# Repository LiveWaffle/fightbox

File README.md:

# FightBox

## Description
The FightBox is a flexible custom built FightBox for fighting games.

## Why I Made it
#### I've Always struggled with wrist pain growing up due to breaking both of them. When i started playing tekken 7 i realized that playing with a traditional FightStick/Controller would cause tons of pain in my wrists. I wanted to design something that was smaller but still use-able and wouldn't hurt my hands after long hours of use.
---

## Pictures

| FightBox Fully Built | PCB |
|--------------------|--------------|
|  |  |

| Schematic | Case  |
|-----------------|----------------|
|  |  |

---
## Bill of Materials (BOM)

| Part                         | Qty | Footprint                 |
|------------------------------|-----|---------------------------|
| 1N4148WT Diode               | 12  | D_DO-35_SOD27_P7.62mm     |
| Cherry MX Switch             | 12  | SW_Cherry_MX_1.00u_PCB    |
| XIAO Seeed ESP32             | 1   | MCU_Seeed_ESP32C3         |
| TicKnot Arcade Button Caps   | 12  | MX Keycap Compatible      |

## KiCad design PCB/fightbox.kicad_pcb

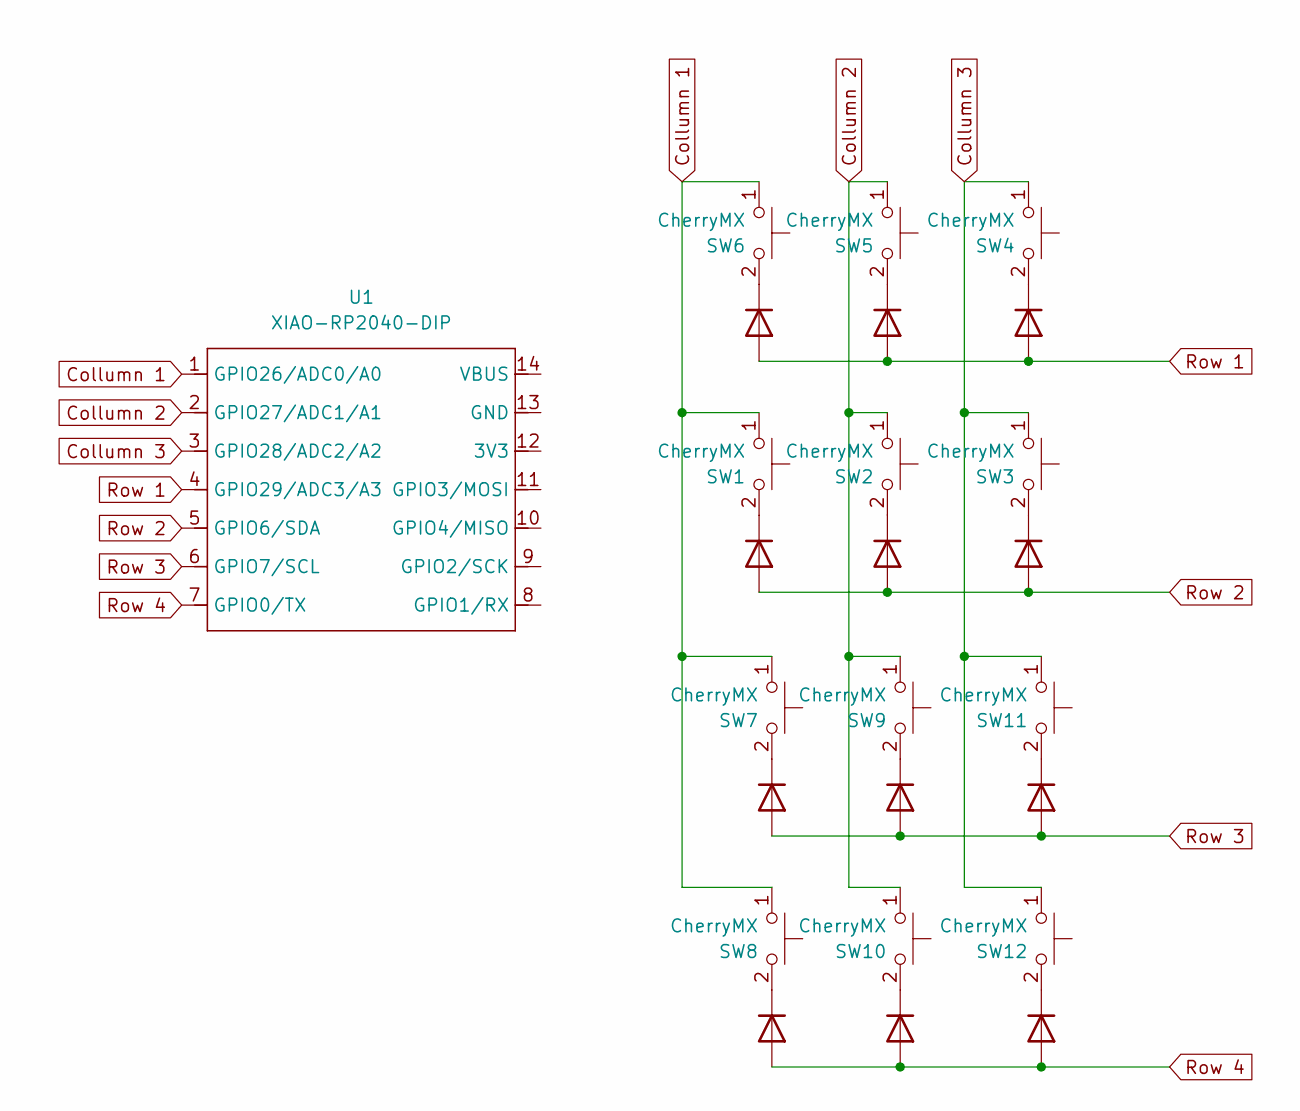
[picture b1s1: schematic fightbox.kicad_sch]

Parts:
D1, D2, D3, D4, D5, D6, D7, D8, D9, D10, D11, D12: 1N4148WT; D_DO-35_SOD27_P7.62mm_Horizontal
SW1, SW2, SW3, SW4, SW5, SW6, SW7, SW8, SW9, SW10, SW11, SW12: CherryMX; SW_Cherry_MX_1.00u_PCB
U1: XIAO-RP2040-DIP; MCU_Seeed_ESP32C3

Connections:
Collumn 1: SW1.1, SW6.1, SW7.1, SW8.1, U1.1 (GPIO26/ADC0/A0)
Collumn 2: SW2.1, SW5.1, SW9.1, SW10.1, U1.2 (GPIO27/ADC1/A1)
Collumn 3: SW3.1, SW4.1, SW11.1, SW12.1, U1.3 (GPIO28/ADC2/A2)
unnamed: D1.1 (K), SW6.2
unnamed: D2.1 (K), SW5.2
unnamed: D3.1 (K), SW4.2
unnamed: D4.1 (K), SW1.2
unnamed: D5.1 (K), SW2.2
unnamed: D6.1 (K), SW3.2
unnamed: D7.1 (K), SW7.2
unnamed: D8.1 (K), SW8.2
unnamed: D9.1 (K), SW9.2
unnamed: D10.1 (K), SW10.2
unnamed: D11.1 (K), SW11.2
unnamed: D12.1 (K), SW12.2
Row 1: D1.2 (A), D2.2 (A), D3.2 (A), U1.4 (GPIO29/ADC3/A3)
Row 2: D4.2 (A), D5.2 (A), D6.2 (A), U1.5 (GPIO6/SDA)
Row 3: D7.2 (A), D9.2 (A), D11.2 (A), U1.6 (GPIO7/SCL)
Row 4: D8.2 (A), D10.2 (A), D12.2 (A), U1.7 (GPIO0/TX)

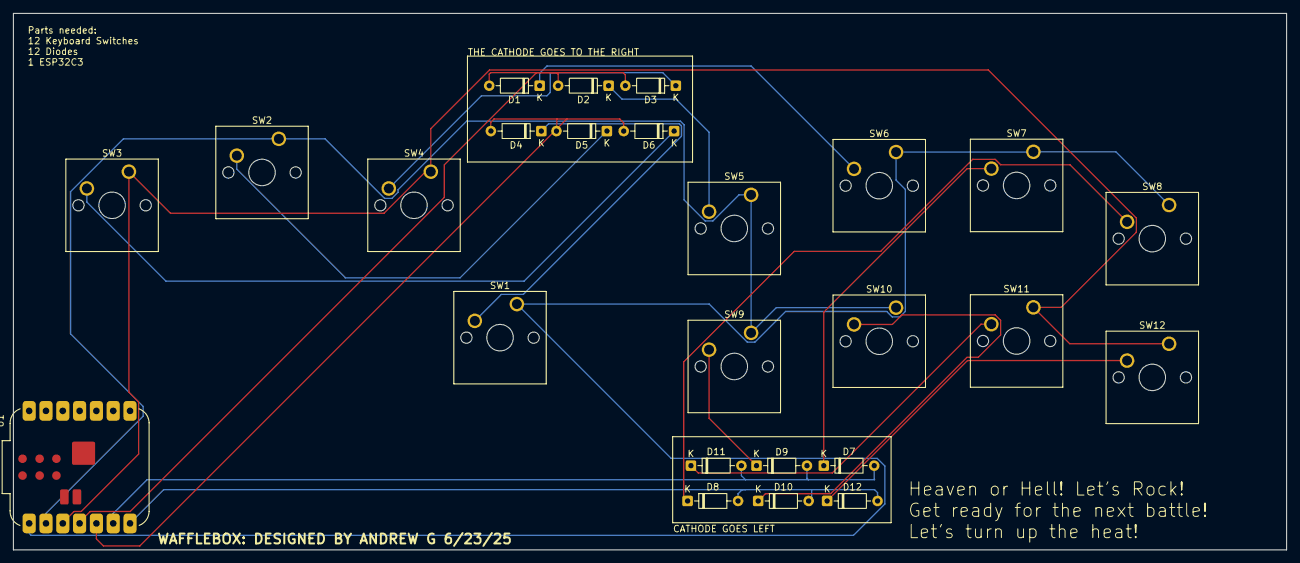
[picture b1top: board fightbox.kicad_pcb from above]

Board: 2 copper layers, 192.3 x 81.0 mm, 25 parts (0 on the bottom side), 19 nets.

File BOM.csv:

"Id";"Designator";"Footprint";"Quantity";"Designation";"Supplier and ref";
1;"D8,D4,D6,D9,D1,D2,D10,D5,D7,D11,D3,D12";"D_DO-35_SOD27_P7.62mm_Horizontal";12;"1N4148WT";;;
2;"SW12,SW2,SW4,SW5,SW3,SW1,SW9,SW6,SW7,SW11,SW8,SW10";"SW_Cherry_MX_1.00u_PCB";12;"CherryMX";;;
3;"U1";"MCU_Seeed_ESP32C3";1;"XIAO-RP2040-DIP";;;

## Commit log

2025-06-25 Add files
